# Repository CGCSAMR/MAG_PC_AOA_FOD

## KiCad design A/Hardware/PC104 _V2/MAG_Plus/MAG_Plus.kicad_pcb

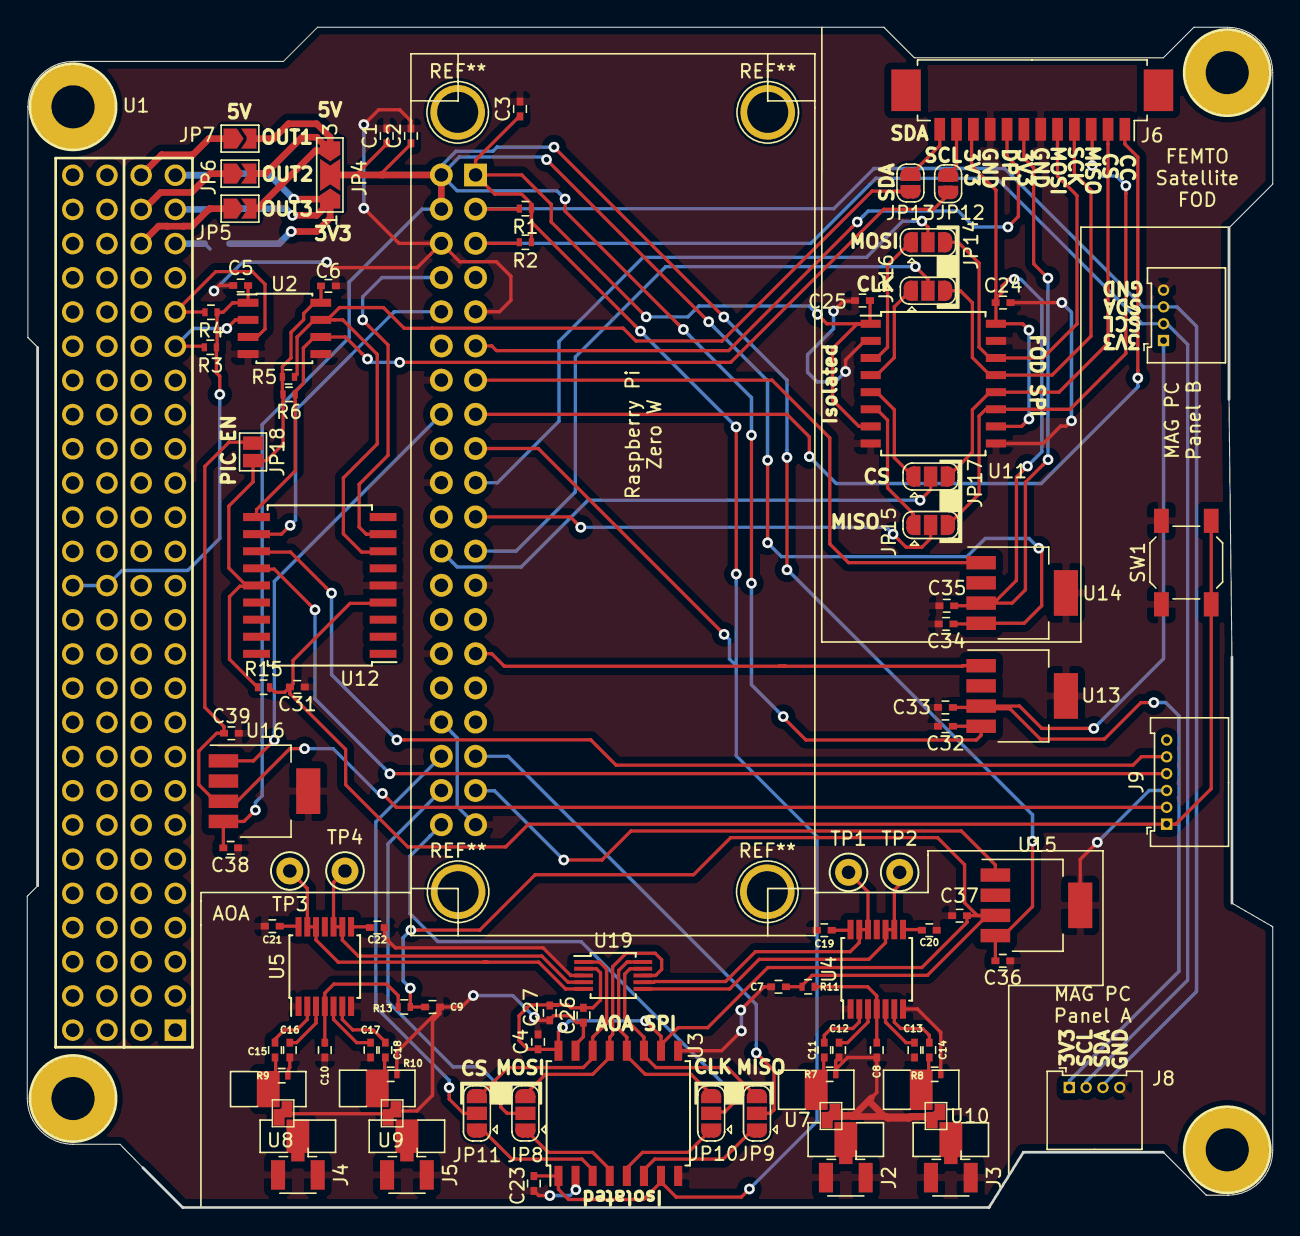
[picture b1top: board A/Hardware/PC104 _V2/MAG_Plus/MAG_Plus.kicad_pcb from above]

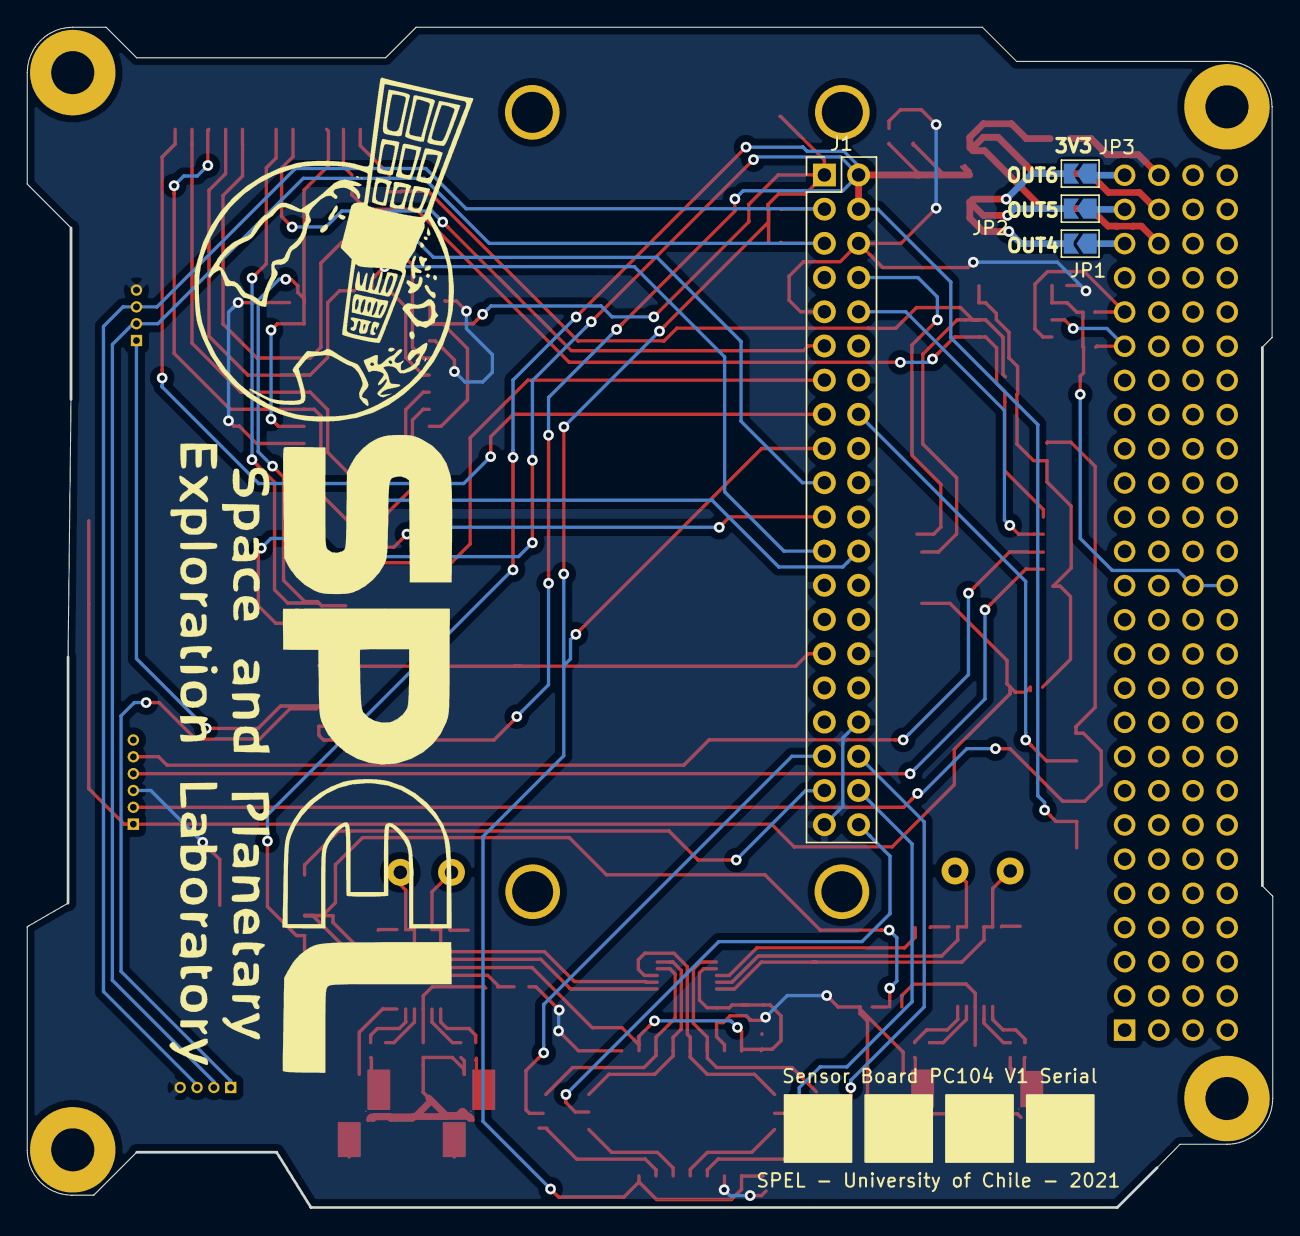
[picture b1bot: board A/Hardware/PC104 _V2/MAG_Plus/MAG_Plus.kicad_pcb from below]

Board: 2 copper layers, 92.5 x 87.7 mm, 97 parts (4 on the bottom side), 86 nets.

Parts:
C1, C2, C3, C4, C5, C6, C23, C24, C25, C26, C27, C31, C32, C33, C34, C35, C36, C37, C38, C39: C; C_0402
C7, C8, C9, C10, C11, C12, C13, C14, C15, C16, C17, C18, C19, C20, C21, C22: C_Small; C_0402
J1: RPi_GPIO; Pin_Header_Straight_2x20_Pitch2.54mm
J2, J3, J4, J5: U.FL-R-SMT(01); U.FL_Hirose_U.FL-R-SMT-1_Vertical
J6: Conn_01x12_Male; Molex_PicoBlade_53261-1271_12x1.25mm_Angled
J7, J8: Conn_01x04_Male; Molex_PicoBlade_53048-0410_04x1.25mm_Angled
J9: Conn_01x06_Male; Molex_PicoBlade_53048-0610_06x1.25mm_Angled
JP1, JP2, JP3, JP5, JP6, JP7: Jumper_2_Open; SolderJumper-2_P1.3mm_Open_TrianglePad1.0x1.5mm
JP4: Jumper_3_Open; SolderJumper-3_P2.0mm_Open_TrianglePad1.0x1.5mm_NumberLabels
JP8, JP9, JP10, JP11, JP14, JP15, JP16, JP17: Jumper_3_Open; SolderJumper-3_P1.3mm_Open_RoundedPad1.0x1.5mm
JP12, JP13: Jumper_2_Open; SolderJumper-2_P1.3mm_Open_RoundedPad1.0x1.5mm
JP18: Jumper_2_Open; SolderJumper-2_P1.3mm_Open_Pad1.0x1.5mm
R1, R2, R3, R4, R5, R6, R15: R; R_0402
R7, R8, R9, R10, R11, R13: R_Small; R_0402
SW1: SW_Push; SW_SPST_SKQG
TP1, TP2, TP3, TP4: TestPoint; Test_Point_Keystone_5000-5004_Miniature
U1: Payload; PC104-Standard
U2: ISO1540; SOIC-8_3.9x4.9mm_Pitch1.27mm
U3, U11: ISO7341C; SOIC-16W_7.5x10.3mm_Pitch1.27mm
U4, U5: AD8302; TSSOP-14_4.4x5mm_Pitch0.65mm
U7, U8, U9, U10: QPQ1906SR
U12: PIC16F1847-I_SO; SOIC-18W_7.5x11.6mm_Pitch1.27mm
U13, U14, U16: LP38693MP-3.3; SOT-223-5
U15: LP38693MP-5.0; SOT-223-5
U19: ADC084S051; MSOP-10_3x3mm_Pitch0.5mm

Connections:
3V3IN: JP1.2, JP2.2, JP3.2, JP4.1
5VIN: JP4.3, JP5.2, JP6.2, JP7.2
ANT1_IN: J2.1, U7.1
ANT1_OUT: C11.1, R7.1, U7.2
ANT2_IN: J3.1, U10.1
ANT2_OUT: C14.1, R8.2, U10.2
ANT3_IN: J4.1, U8.1
ANT3_OUT: C15.1, R9.1, U8.2
ANT4_IN: J5.1, U9.1
ANT4_OUT: C18.1, R10.2, U9.2
AOA_5V: C4.1, C7.2, C9.2, C26.1, C27.1, C37.1, R11.1, R13.1, U3.10, U3.16, U15.3, U19.2
AOA_CLK: JP10.3, U3.12, U19.10
AOA_EN: J1.37, U15.1
AOA_MISO: JP9.3, U3.11, U19.9
AOA_MOSI: JP8.3, U3.13, U19.8
AOA_SS: JP11.3, U3.14, U19.1
CLK0: J1.23, JP16.2
CLK1: J1.40, JP10.2
CSP_SCL: R4.2, U1.43, U2.3
CSP_SDA: R3.2, U1.41, U2.2
FOD_3V3: C24.1, C35.1, J6.7, J6.10, U11.10, U11.16, U14.3
FOD_CC: J1.15, J6.1
FOD_CS: J6.2, JP17.3, U11.12
FOD_DPL: J1.11, J6.8
FOD_EN: J1.13, U14.1
FOD_MISO: J6.3, JP15.3, U11.11
FOD_MOSI: J6.5, JP14.3, U11.14
FOD_SCK: J6.4, JP16.3, U11.13
FOD_SCL: J6.11, JP12.2
FOD_SDA: J6.12, JP13.2
GND: C1.2, C2.2, C3.2, C4.2, C5.2, C6.2, C7.1, C8.1, C9.1, C10.1, C12.1, C13.1, C16.1, C17.1, C19.2, C20.2, C21.2, C22.2, C23.2, C24.2, C25.2, C26.2, C27.2, C31.1, C32.2, C33.2, C34.2, C35.2, C36.2, C37.2, C38.2, C39.2, J1.6, J1.9, J1.14, J1.20, J1.25, J1.30, J1.34, J1.39, J2.2, J3.2, J4.2, J5.2, J6.6, J6.9, J7.4, J8.4, J9.3, R7.2, R8.1, R9.2, R10.1, SW1.1, U2.4, U2.5, U3.2, U3.8, U3.9, U3.15, U4.1, U4.7, U5.1, U5.7, U7.3, U8.3, U9.3, U10.3, U11.2, U11.8, U11.9, U11.15, U12.5, U13.5, U14.5, U15.5, U16.5, U19.3
ICSPCLK: J9.5, U12.12
ICSPDAT: J9.4, U12.13
MAG_3V3: C33.1, J7.1, J8.1, U13.3
MAG_EN: J1.29, U13.1
MCLR: C31.2, J9.1, R15.2, SW1.2, U12.4
MISO0: J1.21, JP15.2
MISO1: J1.35, JP9.2
MOSI0: J1.19, JP14.2
MOSI1: J1.38, JP8.2
unnamed: C8.2, R11.2, U4.4
unnamed: C10.2, R13.2, U5.4
unnamed: C11.2, U4.2
unnamed: C12.2, U4.3
unnamed: C13.2, U4.5
unnamed: C14.2, U4.6
unnamed: C15.2, U5.2
unnamed: C16.2, U5.3
unnamed: C17.2, U5.5
unnamed: C18.2, U5.6
unnamed: C19.1, U4.14
unnamed: C20.1, U4.8
unnamed: C21.1, U5.14
unnamed: C22.1, U5.8
OUT1_3V3: JP1.1, U1.47
OUT2_3V3: JP2.1, U1.49
OUT3_3V3: JP3.1, U1.51
OUT4_5V0: JP5.1, U1.48
OUT5_5V0: JP6.1, U1.50
OUT6_5V0: JP7.1, U1.52
PIC_3V3: C39.1, J9.2, JP18.1, U16.3
PIC_3V3J: C6.1, JP18.2, R5.1, R6.1, R15.1, U2.8, U12.14
PIC_EN: J1.16, U16.1
PIC_SCL: JP12.1, R6.2, U2.6, U12.10
PIC_SDA: JP13.1, R5.2, U2.7, U12.7
RPI_3V3: C3.1, C23.1, C25.1, J1.1, J1.17, R1.1, R2.1, U3.1, U3.7, U11.1, U11.7
RPI_RX: J1.10, U12.11
RPI_SCL: J1.5, J7.2, J8.2, R2.2
RPI_SDA: J1.3, J7.3, J8.3, R1.2
RPI_TX: J1.8, U12.8
SAT_3V3: C5.1, R3.1, R4.1, U1.79, U1.80, U2.1
SS00: J1.24, JP17.2
SS10: J1.36, JP11.2
VIN: C1.1, C2.1, C32.1, C34.1, C36.1, C38.1, J1.2, J1.4, JP4.2, U13.4, U14.4, U15.4, U16.4
VMAG1: TP1.1, U4.12, U4.13, U19.7
VMAG2: TP3.1, U5.12, U5.13, U19.5
VPHS1: TP2.1, U4.9, U4.10, U19.6
VPHS2: TP4.1, U5.9, U5.10, U19.4
iaRPI_CLK: JP10.1, U3.5
iaRPI_MISO: JP9.1, U3.6
iaRPI_MOSI: JP8.1, U3.4
iaRPI_SS0: JP11.1, U3.3
ifRPI_CLK: JP16.1, U11.4
ifRPI_MISO: JP15.1, U11.6
ifRPI_MOSI: JP14.1, U11.3
ifRPI_SS0: JP17.1, U11.5

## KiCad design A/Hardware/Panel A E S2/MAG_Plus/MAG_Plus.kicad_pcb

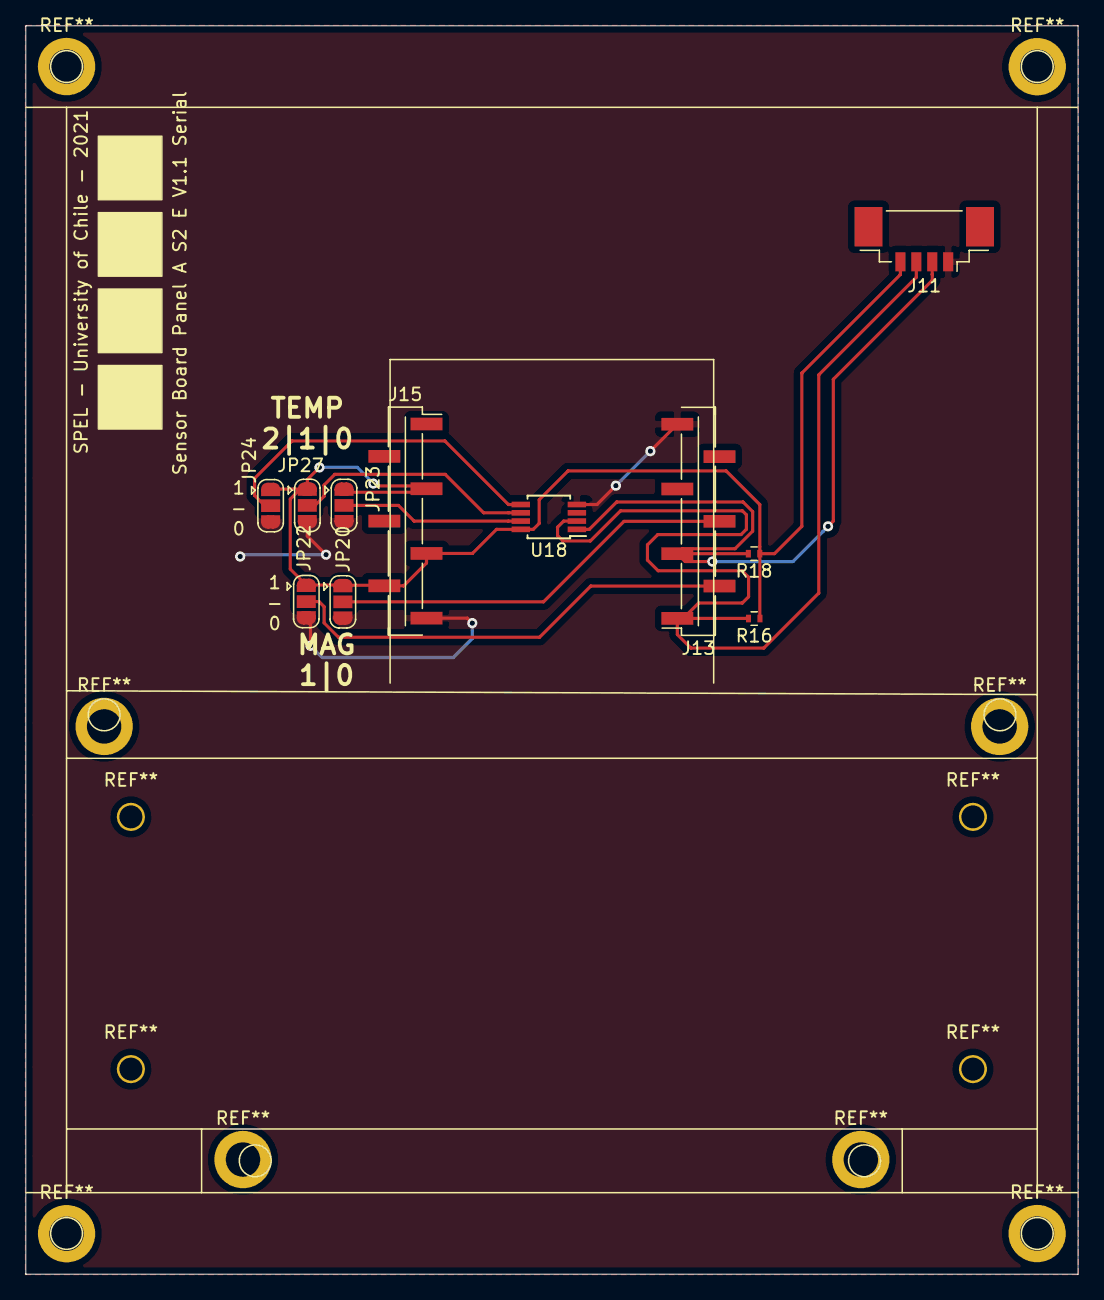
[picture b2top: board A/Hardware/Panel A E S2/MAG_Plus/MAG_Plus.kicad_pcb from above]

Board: 2 copper layers, 82.6 x 98.0 mm, 11 parts (0 on the bottom side), 9 nets.

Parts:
J11: Conn_01x04_Male; Molex_PicoBlade_53398-0471_04x1.25mm_Straight
J13, J15: Conn_01x07_Female; Pin_Header_Straight_1x07_Pitch2.54mm_SMD_Pin1Right
JP20, JP22, JP23, JP24, JP27: Jumper_3_Open; SolderJumper-3_P1.3mm_Open_RoundedPad1.0x1.5mm
R16, R18: R; R_0402
U18: MCP9804_MSOP; MSOP-8_3x3mm_Pitch0.65mm

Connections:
GND: J11.1, J13.7, J15.7, JP20.3, JP22.3, JP23.3, JP24.3, JP27.3, U18.4
MAG2_A0: JP23.2, U18.7
MAG2_A1: JP27.2, U18.6
MAG2_A2: JP24.2, U18.5
MAG2_BIT0: J13.4, JP20.2
MAG2_BIT1: J13.2, JP22.2
MAG_3V3: J11.4, J15.3, J15.5, J15.6, JP20.1, JP22.1, JP23.1, JP24.1, JP27.1, R16.1, R18.1, U18.8
RPI_SCL: J11.3, J13.1, R16.2, U18.2
RPI_SDA: J11.2, J13.3, R18.2, U18.1

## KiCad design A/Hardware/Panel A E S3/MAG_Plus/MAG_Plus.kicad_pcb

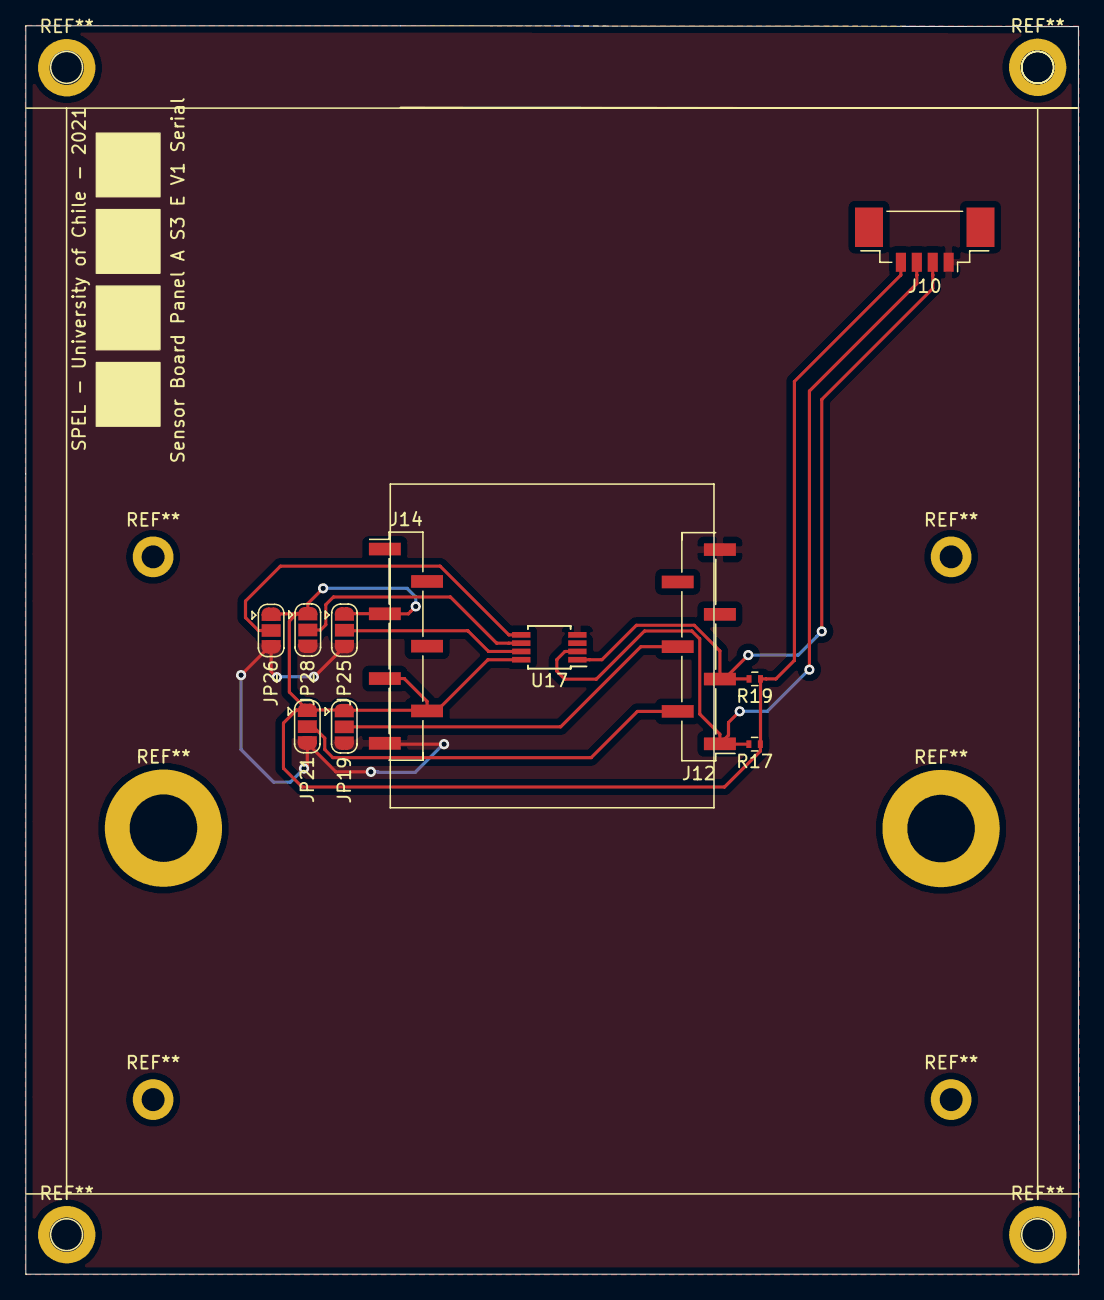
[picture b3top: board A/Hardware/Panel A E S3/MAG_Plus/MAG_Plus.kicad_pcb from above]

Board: 2 copper layers, 82.6 x 98.0 mm, 11 parts (0 on the bottom side), 9 nets.

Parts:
J10: Conn_01x04_Male; Molex_PicoBlade_53398-0471_04x1.25mm_Straight
J12, J14: Conn_01x07_Female; Pin_Header_Straight_1x07_Pitch2.54mm_SMD_Pin1Left
JP19, JP21, JP25, JP26, JP28: Jumper_3_Open; SolderJumper-3_P1.3mm_Open_RoundedPad1.0x1.5mm
R17, R19: R; R_0402
U17: MCP9804_MSOP; MSOP-8_3x3mm_Pitch0.65mm

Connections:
GND: J10.1, J12.7, J14.7, JP19.3, JP21.3, JP25.3, JP26.3, JP28.3, U17.4
MAG1_A0: JP25.2, U17.7
MAG1_A1: JP28.2, U17.6
MAG1_A2: JP26.2, U17.5
MAG1_BIT0: J12.4, JP19.2
MAG1_BIT1: J12.2, JP21.2
MAG_3V3: J10.4, J14.3, J14.5, J14.6, JP19.1, JP21.1, JP25.1, JP26.1, JP28.1, R17.1, R19.1, U17.8
RPI_SCL: J10.3, J12.1, R17.2, U17.2
RPI_SDA: J10.2, J12.3, R19.2, U17.1

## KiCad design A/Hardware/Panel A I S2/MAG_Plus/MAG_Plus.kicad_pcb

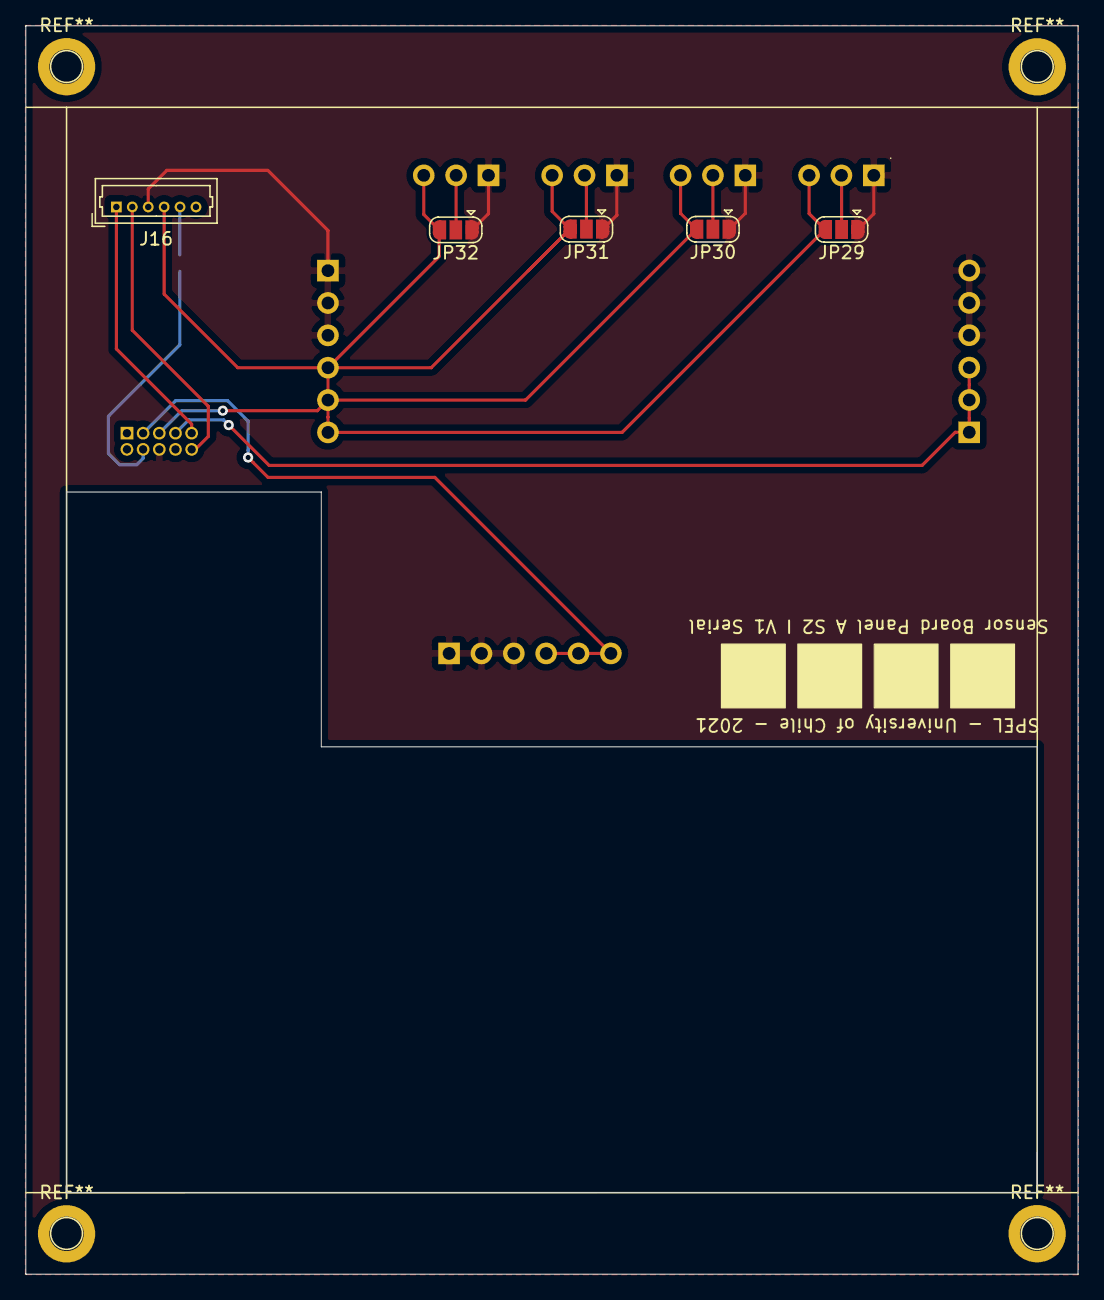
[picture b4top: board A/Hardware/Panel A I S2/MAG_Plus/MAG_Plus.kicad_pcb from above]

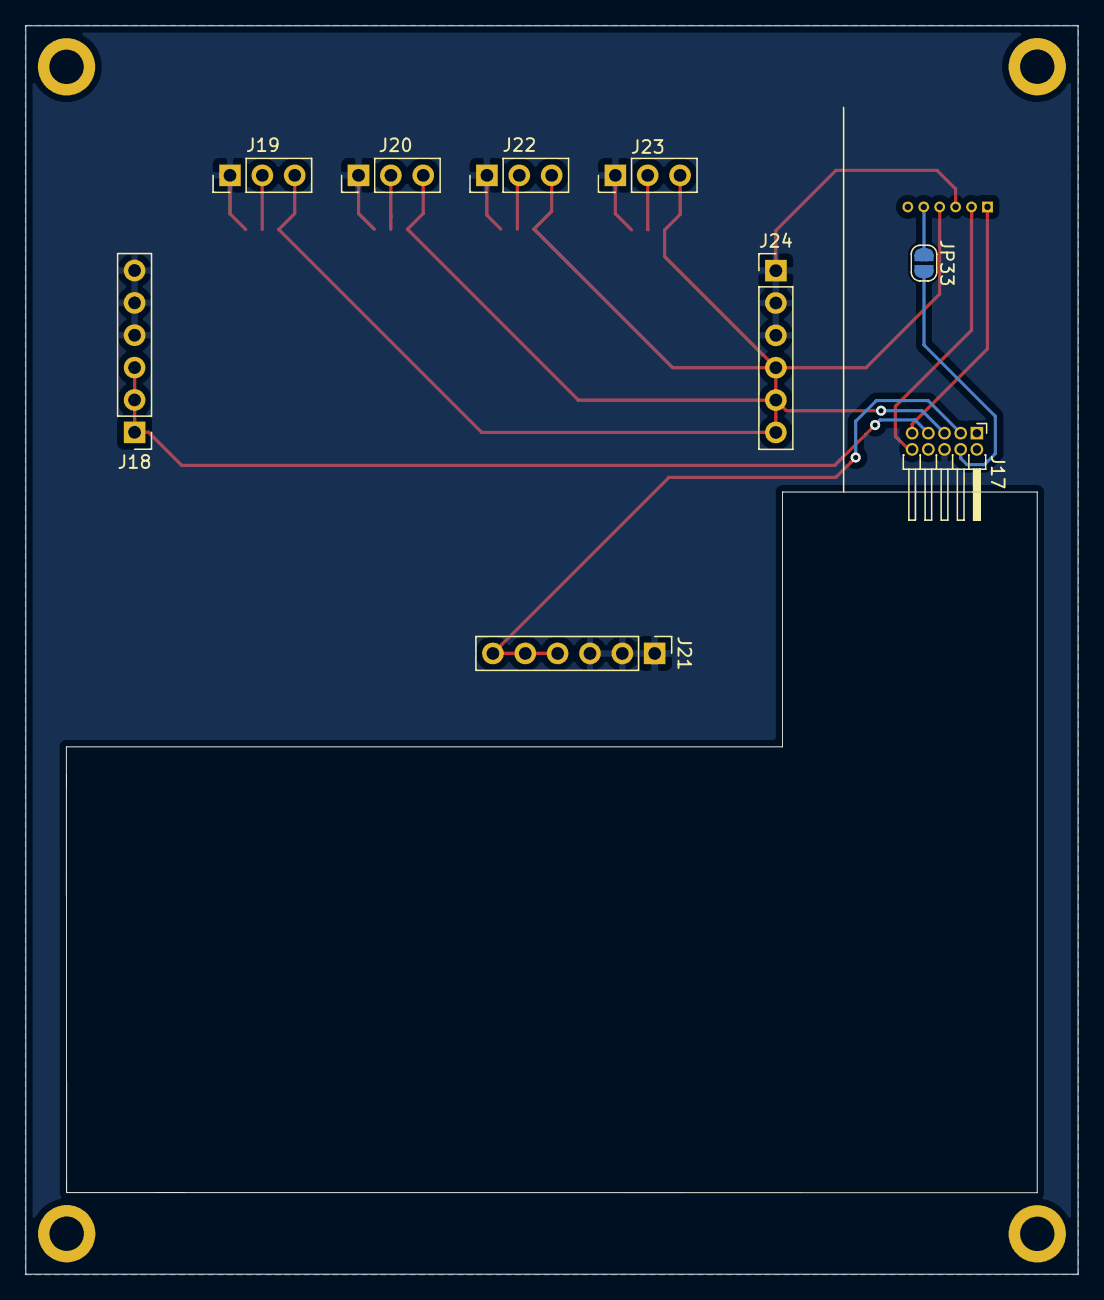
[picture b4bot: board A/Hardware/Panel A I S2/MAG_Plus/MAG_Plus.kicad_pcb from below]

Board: 2 copper layers, 82.6 x 98.0 mm, 14 parts (9 on the bottom side), 12 nets.

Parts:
J16: Conn_01x06_Male; Molex_PicoBlade_53047-0610_06x1.25mm_Straight
J17: Conn_02x05_Counter_Clockwise; Pin_Header_Angled_2x05_Pitch1.27mm
J18, J21, J24: Conn_01x06_Male; Pin_Header_Straight_1x06_Pitch2.54mm
J19, J20, J22, J23: Conn_01x03_Male; Pin_Header_Straight_1x03_Pitch2.54mm
JP29, JP30, JP31, JP32: Jumper_3_Open; SolderJumper-3_P1.3mm_Open_RoundedPad1.0x1.5mm
JP33: Jumper_2_Open; SolderJumper-2_P1.3mm_Open_RoundedPad1.0x1.5mm

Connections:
ENN: J20.2, JP30.2
ENP: J23.2, JP32.2
GND: J16.3, J17.6, J18.4, J18.5, J18.6, J19.1, J20.1, J21.1, J21.2, J21.3, J22.1, J23.1, J24.1, J24.2, J24.3, JP29.1, JP30.1, JP31.1, JP32.1
LPS_3V3: J16.5, JP33.1
LPS_3V3J: J17.4, JP33.2
LPS_5V: J16.4, J17.5, J19.3, J20.3, J22.3, J23.3, J24.4, J24.5, J24.6, JP29.3, JP30.3, JP31.3, JP32.3
LPS_RX: J16.1, J17.9
LPS_TX: J16.2, J17.10
PSN: J19.2, JP29.2
PSP: J22.2, JP31.2
VNEG: J17.7, J18.1, J18.2, J18.3
VPOS: J17.3, J21.4, J21.5, J21.6
